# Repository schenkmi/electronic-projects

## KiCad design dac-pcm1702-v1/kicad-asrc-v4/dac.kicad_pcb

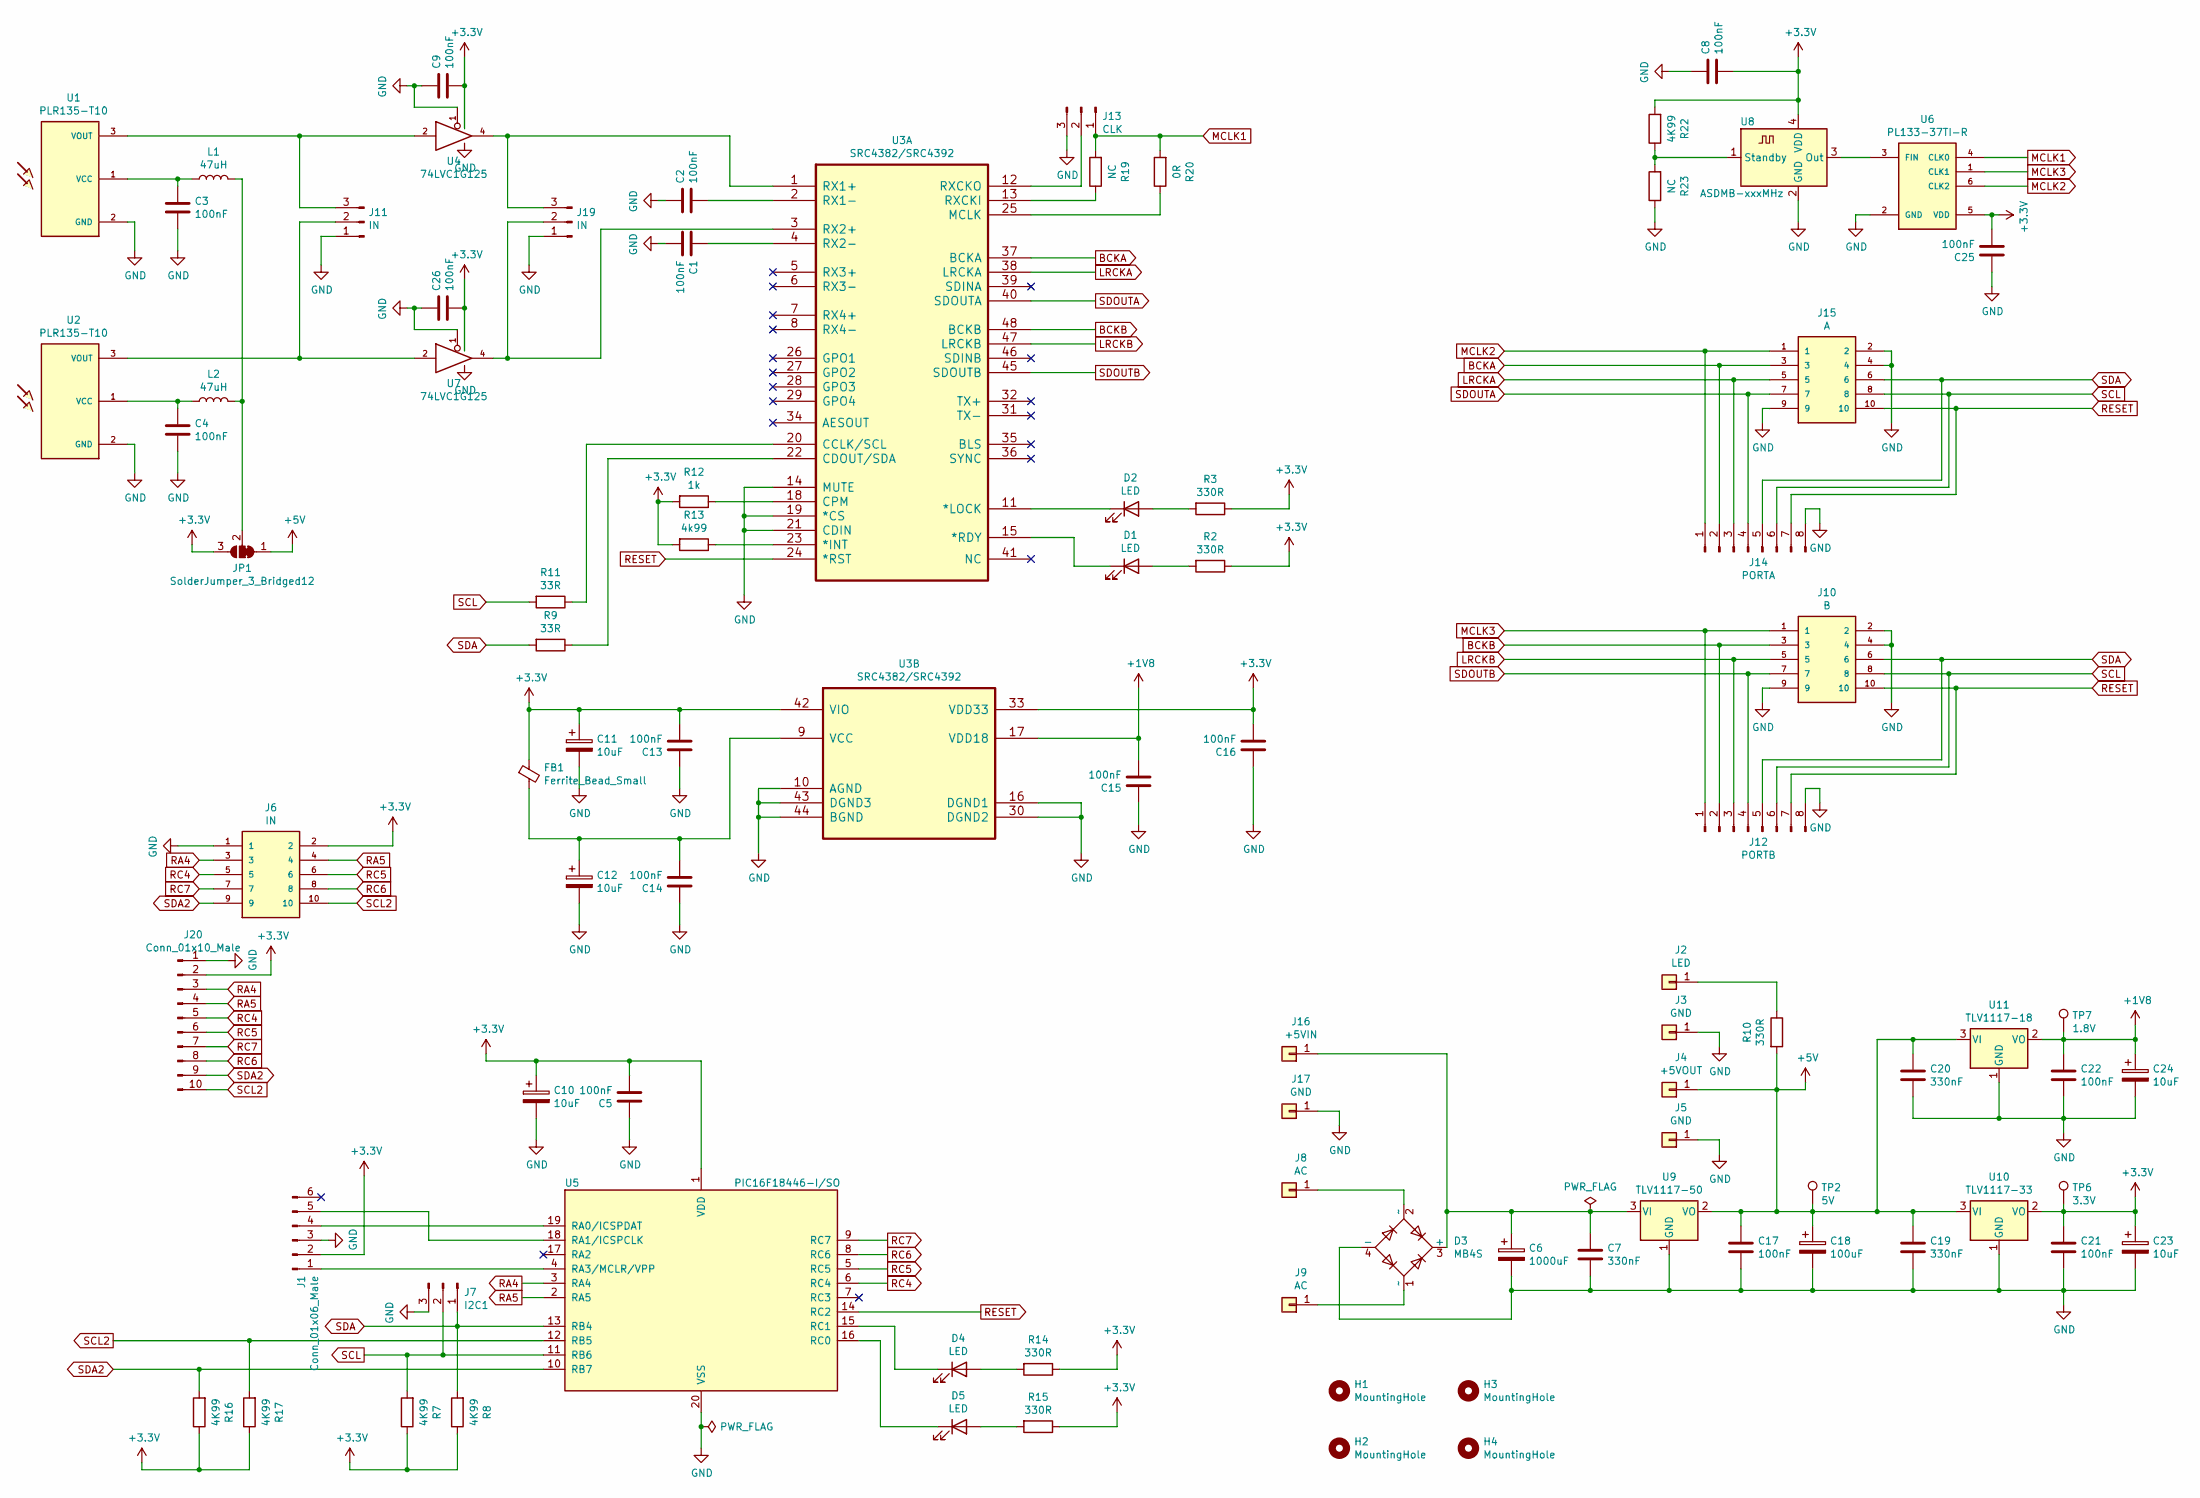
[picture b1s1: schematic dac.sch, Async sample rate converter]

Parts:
C1, C2, C3, C4, C5, C8, C9, C13, C14, C15, C16, C25, C26: 100nF; C_0603_1608Metric_Pad1.08x0.95mm_HandSolder
C6: 1000uF; CP_Radial_D12.5mm_P5.00mm
C7, C19, C20: 330nF; C_0805_2012Metric_Pad1.18x1.45mm_HandSolder
C10, C11, C12, C23, C24: 10uF; CP_EIA-3528-21_Kemet-B_Pad1.50x2.35mm_HandSolder
C17, C21, C22: 100nF; C_0805_2012Metric_Pad1.18x1.45mm_HandSolder
C18: 100uF; CP_Radial_D8.0mm_P3.50mm
D1, D2, D4, D5: LED; LED_0805_2012Metric_Pad1.15x1.40mm_HandSolder
D3: MB4S; TO-269AA
FB1: Ferrite_Bead_Small; C_0603_1608Metric_Pad1.08x0.95mm_HandSolder
H1, H2, H3, H4: MountingHole; MountingHole_3.2mm_M3
J1: Conn_01x06_Male; PinHeader_1x06_P2.54mm_Vertical
J2: LED; Pin_D1.0mm_L10.0mm
J3, J5, J17: GND; Pin_D1.0mm_L10.0mm
J4: +5VOUT; Pin_D1.0mm_L10.0mm
J6: IN; TE_CONN_RCPT_10POS_0.1_TIN_PCB
J7: I2C1; PinHeader_1x03_P2.54mm_Vertical
J8, J9: AC; Pin_D1.0mm_L10.0mm
J10: B; TE_CONN_RCPT_10POS_0.1_TIN_PCB
J11, J19: IN; PinHeader_1x03_P2.54mm_Vertical
J12: PORTB; PinHeader_1x08_P2.54mm_Vertical
J13: CLK; PinHeader_1x03_P2.54mm_Vertical
J14: PORTA; PinHeader_1x08_P2.54mm_Vertical
J15: A; TE_CONN_RCPT_10POS_0.1_TIN_PCB
J16: +5VIN; Pin_D1.0mm_L10.0mm
J20: Conn_01x10_Male; PinHeader_2x05_P2.54mm_Vertical
JP1: SolderJumper_3_Bridged12; SolderJumper-3_P1.3mm_Bridged12_RoundedPad1.0x1.5mm_NumberL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
L1, L2: 47uH; L_0805_2012Metric_Pad1.05x1.20mm_HandSolder
R2, R3, R14, R15: 330R; R_0603_1608Metric_Pad0.98x0.95mm_HandSolder
R7, R8, R16, R17, R22: 4K99; R_0603_1608Metric_Pad0.98x0.95mm_HandSolder
R9, R11: 33R; R_0603_1608Metric_Pad0.98x0.95mm_HandSolder
R10: 330R; R_0805_2012Metric_Pad1.20x1.40mm_HandSolder
R12: 1k; R_0603_1608Metric_Pad0.98x0.95mm_HandSolder
R13: 4k99; R_0603_1608Metric_Pad0.98x0.95mm_HandSolder
R19, R23: NC; R_0603_1608Metric_Pad0.98x0.95mm_HandSolder
R20: 0R; R_0603_1608Metric_Pad0.98x0.95mm_HandSolder
TP2: 5V; TestPoint_Pad_D1.0mm
TP6: 3.3V; TestPoint_Pad_D1.0mm
TP7: 1.8V; TestPoint_Pad_D1.0mm
U1, U2: PLR135-T10; PLR135-T10_PLT133-T10W
U3: SRC4382/SRC4392; TQFP-48_7x7mm_P0.5mm
U4, U7: 74LVC1G125; SOT-353_SC-70-5_Handsoldering
U5: PIC16F18446-I/SO; SOIC-20W_7.5x12.8mm_P1.27mm
U6: PL133-37TI-R; SOT-23-6
U8: ASDMB-xxxMHz; Oscillator_SMD_EuroQuartz_XO91-4Pin_7.0x5.0mm_HandSoldering
U9: TLV1117-50; SOT-223-3_TabPin2
U10: TLV1117-33; SOT-223-3_TabPin2
U11: TLV1117-18; SOT-223-3_TabPin2

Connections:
+1V8: C15.2, C22.1, C24.1, TP7.1, U3.17 (VDD18), U11.2 (VO)
+3V3: C5.2, C8.1, C9.1, C10.1, C11.1, C13.2, C16.2, C21.1, C23.1, C25.2, C26.1, FB1.1, J1.2, J6.2, J20.2, JP1.3 (B), R2.1, R3.1, R7.1, R8.1, R12.2, R13.2, R14.1, R15.1, R16.1, R17.1, R22.2, TP6.1, U3.33 (VDD33), U3.42 (VIO), U4.5 (VCC), U5.1 (VDD), U6.5 (VDD), U7.5 (VCC), U8.4 (VDD), U10.2 (VO)
+5V: C17.1, C18.1, C19.1, C20.1, J4.1, JP1.1 (A), R10.2, TP2.1, U9.2 (VO), U10.3 (VI), U11.3 (VI)
BCKA: J14.2, J15.3, U3.37 (BCKA)
BCKB: J10.3, J12.2, U3.48 (BCKB)
GND: C1.1, C2.2, C3.1, C4.1, C5.1, C6.2, C7.2, C8.2, C9.2, C10.2, C11.2, C12.2, C13.1, C14.1, C15.1, C16.1, C17.2, C18.2, C19.2, C20.2, C21.2, C22.2, C23.2, C24.2, C25.1, C26.2, D3.4 (-), J1.3, J3.1, J5.1, J6.1, J7.3, J10.2, J10.4, J10.9, J11.1, J12.8, J13.3, J14.8, J15.2, J15.4, J15.9, J17.1, J19.1, J20.1, R23.1, U1.2 (GND), U2.2 (GND), U3.10 (AGND), U3.14 (MUTE), U3.16 (DGND1), U3.19 (*CS), U3.21 (CDIN), U3.30 (DGND2), U3.43 (DGND3), U3.44 (BGND), U4.1, U4.3 (GND), U5.20 (VSS), U6.2 (GND), U7.1, U7.3 (GND), U8.2 (GND), U9.1 (GND), U10.1 (GND), U11.1 (GND)
LRCKA: J14.3, J15.5, U3.38 (LRCKA)
LRCKB: J10.5, J12.3, U3.47 (LRCKB)
MCLK1: J13.1, R19.2, R20.2, U6.4 (CLK0)
MCLK2: J14.1, J15.1, U6.6 (CLK2)
MCLK3: J10.1, J12.1, U6.1 (CLK1)
unnamed: C1.2, U3.4 (RX2-)
unnamed: C2.1, U3.2 (RX1-)
unnamed: C3.2, L1.1, U1.1 (VCC)
unnamed: C4.2, L2.1, U2.1 (VCC)
unnamed: C6.1, C7.1, D3.3 (+), J16.1, U9.3 (VI)
unnamed: C12.1, C14.2, FB1.2, U3.9 (VCC)
unnamed: D1.1 (K), U3.15 (*RDY)
unnamed: D1.2 (A), R2.2
unnamed: D2.1 (K), U3.11 (*LOCK)
unnamed: D2.2 (A), R3.2
unnamed: D3.1 (~~), J9.1
unnamed: D3.2 (~~), J8.1
unnamed: D4.1 (K), U5.15 (RC1)
unnamed: D4.2 (A), R14.2
unnamed: D5.1 (K), U5.16 (RC0)
unnamed: D5.2 (A), R15.2
unnamed: J1.1, U5.4 (RA3/MCLR/VPP)
unnamed: J1.4, U5.19 (RA0/ICSPDAT)
unnamed: J1.5, U5.18 (RA1/ICSPCLK)
unnamed: J2.1, R10.1
unnamed: J11.2, U2.3 (VOUT), U7.2
unnamed: J11.3, U1.3 (VOUT), U4.2
unnamed: J13.2, U3.12 (RXCKO)
unnamed: J19.2, U3.3 (RX2+), U7.4
unnamed: J19.3, U3.1 (RX1+), U4.4
unnamed: JP1.2 (C), L1.2, L2.2
unnamed: R9.1, U3.22 (CDOUT/SDA)
unnamed: R11.1, U3.20 (CCLK/SCL)
unnamed: R12.1, U3.18 (CPM)
unnamed: R13.1, U3.23 (*INT)
unnamed: R19.1, U3.13 (RXCKI)
unnamed: R20.1, U3.25 (MCLK)
unnamed: R22.1, R23.2, U8.1 (Standby)
unnamed: U6.3 (FIN), U8.3 (Out)
RA4: J6.3, J20.3, U5.3 (RA4)
RA5: J6.4, J20.4, U5.2 (RA5)
RC4: J6.5, J20.5, U5.6 (RC4)
RC5: J6.6, J20.6, U5.5 (RC5)
RC6: J6.8, J20.8, U5.8 (RC6)
RC7: J6.7, J20.7, U5.9 (RC7)
RESET: J10.10, J12.7, J14.7, J15.10, U3.24 (*RST), U5.14 (RC2)
SCL: J7.2, J10.8, J12.6, J14.6, J15.8, R7.2, R11.2, U5.11 (RB6)
SCL2: J6.10, J20.10, R17.2, U5.12 (RB5)
SDA: J7.1, J10.6, J12.5, J14.5, J15.6, R8.2, R9.2, U5.13 (RB4)
SDA2: J6.9, J20.9, R16.2, U5.10 (RB7)
SDOUTA: J14.4, J15.7, U3.40 (SDOUTA)
SDOUTB: J10.7, J12.4, U3.45 (SDOUTB)

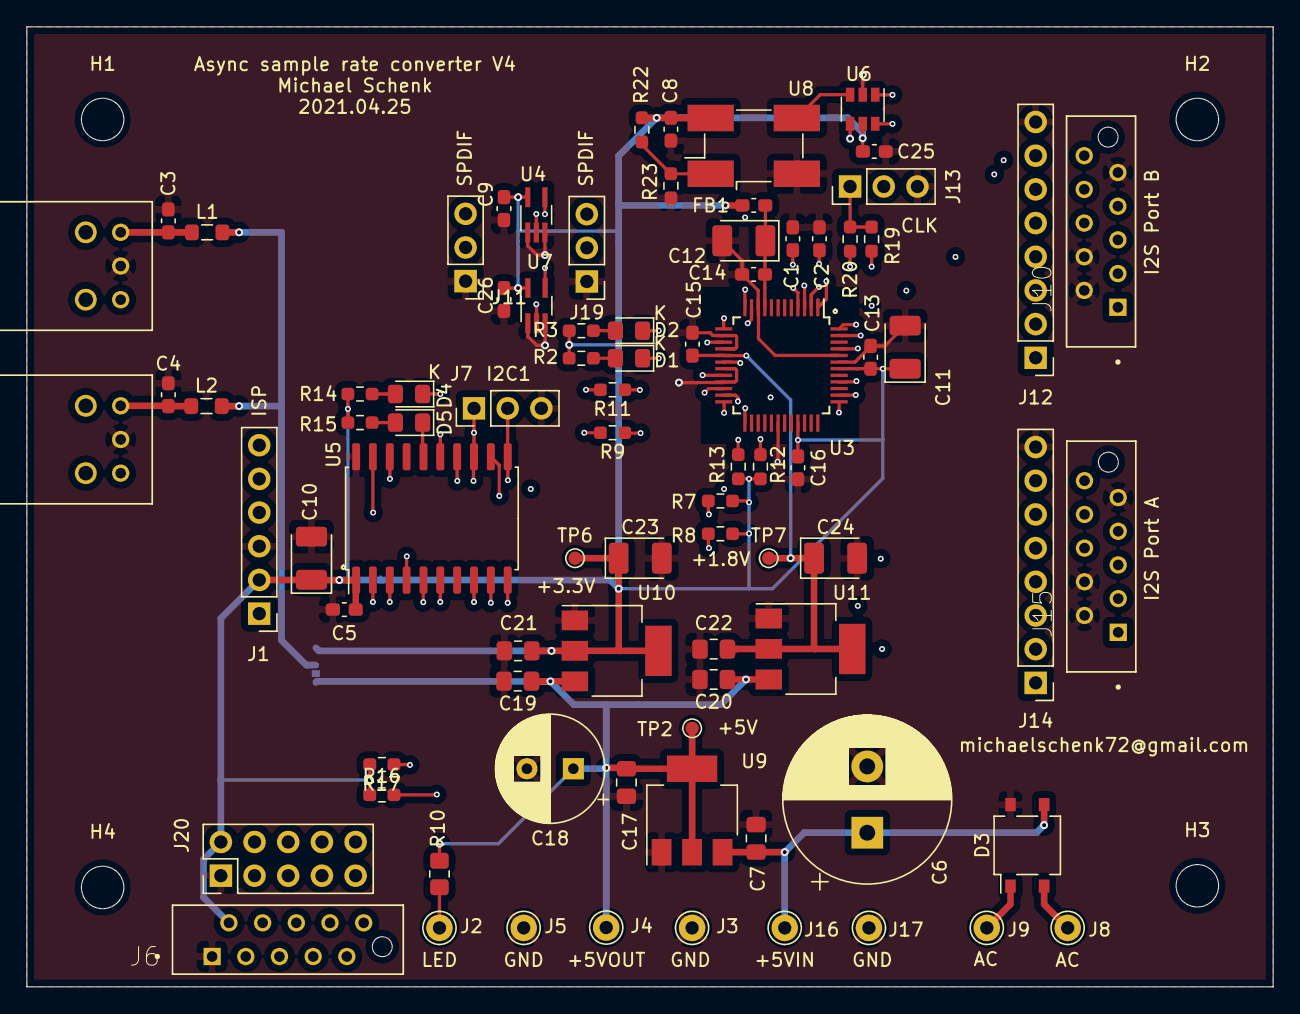
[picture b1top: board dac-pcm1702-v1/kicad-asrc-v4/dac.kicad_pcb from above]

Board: 4 copper layers, 94.0 x 72.4 mm, 89 parts (1 on the bottom side), 58 nets.

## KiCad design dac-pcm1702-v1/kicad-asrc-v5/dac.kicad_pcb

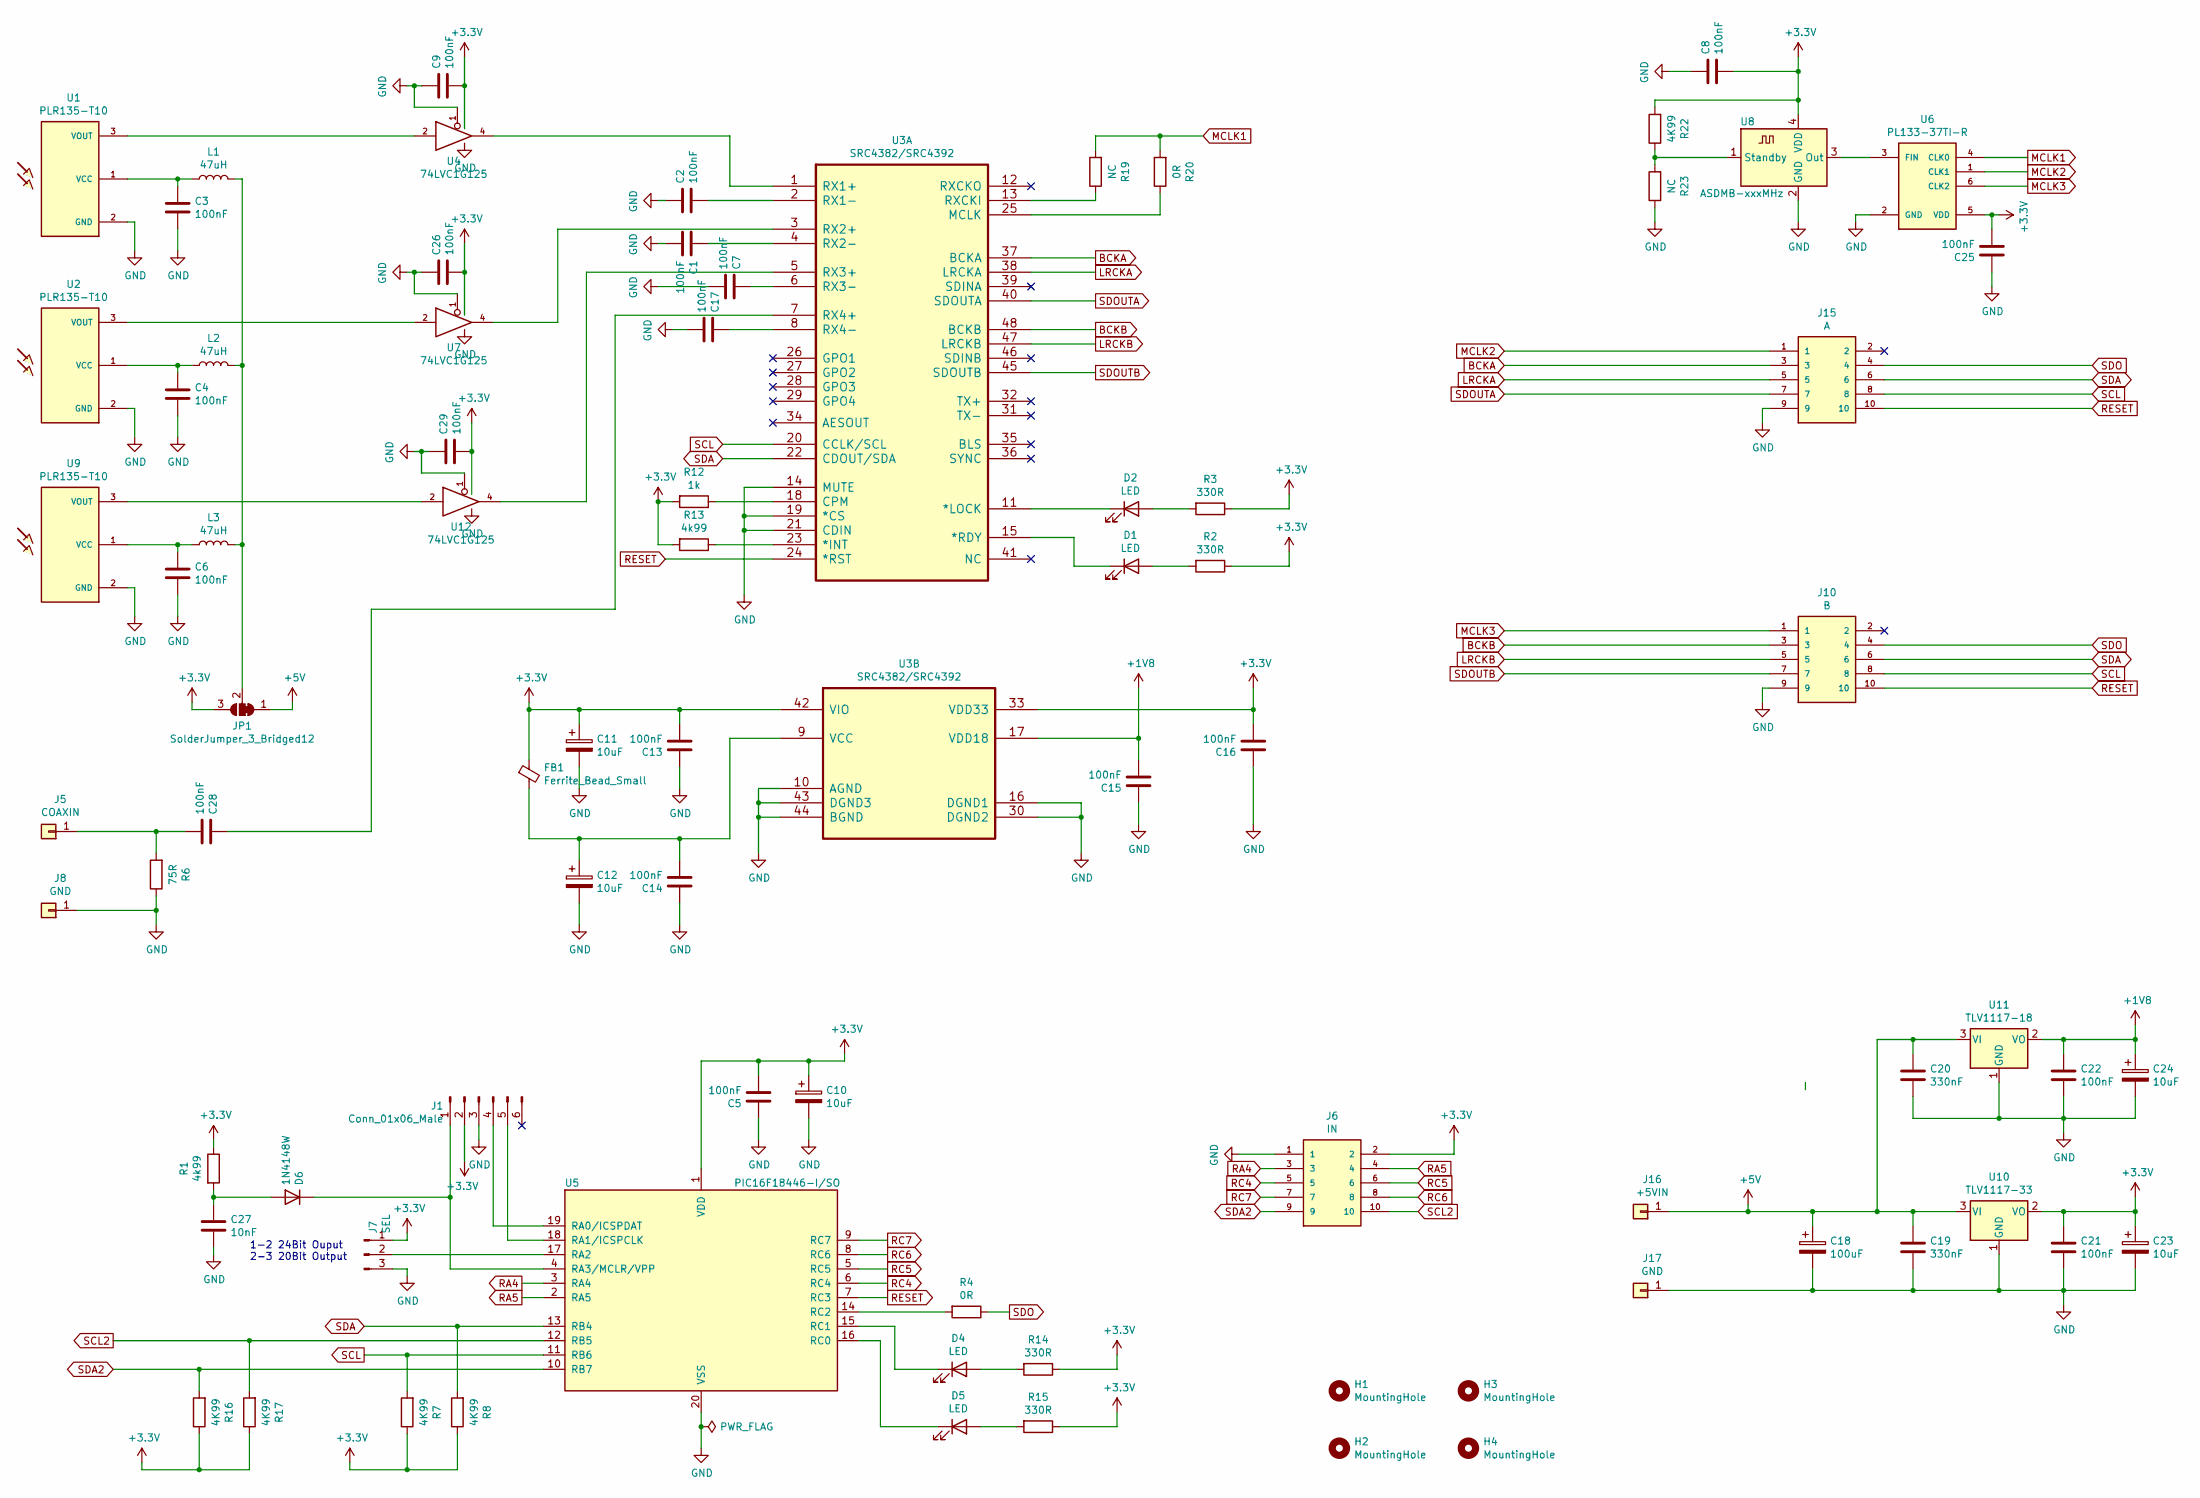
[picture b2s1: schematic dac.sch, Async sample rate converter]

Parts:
C1, C2, C3, C4, C5, C6, C7, C8, C9, C13, C14, C15, C16, C17, C25, C26, C28, C29: 100nF; C_0603_1608Metric_Pad1.08x0.95mm_HandSolder
C10, C11, C12, C23, C24: 10uF; CP_EIA-3528-21_Kemet-B_Pad1.50x2.35mm_HandSolder
C18: 100uF; CP_Radial_D8.0mm_P3.50mm
C19, C20: 330nF; C_0805_2012Metric_Pad1.18x1.45mm_HandSolder
C21, C22: 100nF; C_0805_2012Metric_Pad1.18x1.45mm_HandSolder
C27: 10nF; C_0603_1608Metric_Pad1.08x0.95mm_HandSolder
D1, D2, D4, D5: LED; LED_0805_2012Metric_Pad1.15x1.40mm_HandSolder
D6: 1N4148W; D_SOD-123
FB1: Ferrite_Bead_Small; C_0603_1608Metric_Pad1.08x0.95mm_HandSolder
H1, H2, H3, H4: MountingHole; MountingHole_3.2mm_M3
J1: Conn_01x06_Male; PinHeader_1x06_P2.54mm_Vertical
J5: COAXIN; Pin_D1.0mm_L10.0mm
J6: IN; TE_CONN_RCPT_10POS_0.1_TIN_PCB
J7: SEL; PinHeader_1x03_P2.54mm_Vertical
J8, J17: GND; Pin_D1.0mm_L10.0mm
J10: B; TE_CONN_RCPT_10POS_0.1_TIN_PCB
J15: A; TE_CONN_RCPT_10POS_0.1_TIN_PCB
J16: +5VIN; Pin_D1.0mm_L10.0mm
JP1: SolderJumper_3_Bridged12; SolderJumper-3_P1.3mm_Bridged12_RoundedPad1.0x1.5mm_NumberL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
L1, L2, L3: 47uH; L_0805_2012Metric_Pad1.05x1.20mm_HandSolder
R1, R13: 4k99; R_0603_1608Metric_Pad0.98x0.95mm_HandSolder
R2, R3, R14, R15: 330R; R_0603_1608Metric_Pad0.98x0.95mm_HandSolder
R4, R20: 0R; R_0603_1608Metric_Pad0.98x0.95mm_HandSolder
R6: 75R; R_0603_1608Metric_Pad0.98x0.95mm_HandSolder
R7, R8, R16, R17, R22: 4K99; R_0603_1608Metric_Pad0.98x0.95mm_HandSolder
R12: 1k; R_0603_1608Metric_Pad0.98x0.95mm_HandSolder
R19, R23: NC; R_0603_1608Metric_Pad0.98x0.95mm_HandSolder
U1, U2, U9: PLR135-T10; PLR135-T10_PLT133-T10W
U3: SRC4382/SRC4392; TQFP-48_7x7mm_P0.5mm
U4, U7, U12: 74LVC1G125; SOT-353_SC-70-5_Handsoldering
U5: PIC16F18446-I/SO; SOIC-20W_7.5x12.8mm_P1.27mm
U6: PL133-37TI-R; SOT-23-6
U8: ASDMB-xxxMHz; Oscillator_SMD_EuroQuartz_XO91-4Pin_7.0x5.0mm_HandSoldering
U10: TLV1117-33; SOT-223-3_TabPin2
U11: TLV1117-18; SOT-223-3_TabPin2

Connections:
+1V8: C15.2, C22.1, C24.1, U3.17 (VDD18), U11.2 (VO)
+3V3: C5.2, C8.1, C9.1, C10.1, C11.1, C13.2, C16.2, C21.1, C23.1, C25.2, C26.1, C29.1, FB1.1, J1.2, J6.2, J7.1, JP1.3 (B), R1.1, R2.1, R3.1, R7.1, R8.1, R12.2, R13.2, R14.1, R15.1, R16.1, R17.1, R22.2, U3.33 (VDD33), U3.42 (VIO), U4.5 (VCC), U5.1 (VDD), U6.5 (VDD), U7.5 (VCC), U8.4 (VDD), U10.2 (VO), U12.5 (VCC)
+5V: C18.1, C19.1, C20.1, J16.1, JP1.1 (A), U10.3 (VI), U11.3 (VI)
BCKA: J15.3, U3.37 (BCKA)
BCKB: J10.3, U3.48 (BCKB)
GND: C1.1, C2.2, C3.1, C4.1, C5.1, C6.1, C7.1, C8.2, C9.2, C10.2, C11.2, C12.2, C13.1, C14.1, C15.1, C16.1, C17.1, C18.2, C19.2, C20.2, C21.2, C22.2, C23.2, C24.2, C25.1, C26.2, C27.2, C29.2, J1.3, J6.1, J7.3, J8.1, J10.9, J15.9, J17.1, R6.1, R23.1, U1.2 (GND), U2.2 (GND), U3.10 (AGND), U3.14 (MUTE), U3.16 (DGND1), U3.19 (*CS), U3.21 (CDIN), U3.30 (DGND2), U3.43 (DGND3), U3.44 (BGND), U4.1, U4.3 (GND), U5.20 (VSS), U6.2 (GND), U7.1, U7.3 (GND), U8.2 (GND), U9.2 (GND), U10.1 (GND), U11.1 (GND), U12.1, U12.3 (GND)
LRCKA: J15.5, U3.38 (LRCKA)
LRCKB: J10.5, U3.47 (LRCKB)
MCLK1: R19.2, R20.2, U6.4 (CLK0)
MCLK2: J15.1, U6.1 (CLK1)
MCLK3: J10.1, U6.6 (CLK2)
unnamed: C1.2, U3.4 (RX2-)
unnamed: C2.1, U3.2 (RX1-)
unnamed: C3.2, L1.1, U1.1 (VCC)
unnamed: C4.2, L2.1, U2.1 (VCC)
unnamed: C6.2, L3.1, U9.1 (VCC)
unnamed: C7.2, U3.6 (RX3-)
unnamed: C12.1, C14.2, FB1.2, U3.9 (VCC)
unnamed: C17.2, U3.8 (RX4-)
unnamed: C27.1, D6.2 (A), R1.2
unnamed: C28.1, J5.1, R6.2
unnamed: C28.2, U3.7 (RX4+)
unnamed: D1.1 (K), U3.15 (*RDY)
unnamed: D1.2 (A), R2.2
unnamed: D2.1 (K), U3.11 (*LOCK)
unnamed: D2.2 (A), R3.2
unnamed: D4.1 (K), U5.15 (RC1)
unnamed: D4.2 (A), R14.2
unnamed: D5.1 (K), U5.16 (RC0)
unnamed: D5.2 (A), R15.2
unnamed: D6.1 (K), J1.1, U5.4 (RA3/MCLR/VPP)
unnamed: J1.4, U5.19 (RA0/ICSPDAT)
unnamed: J1.5, U5.18 (RA1/ICSPCLK)
unnamed: J7.2, U5.17 (RA2)
unnamed: JP1.2 (C), L1.2, L2.2, L3.2
unnamed: R4.2, U5.14 (RC2)
unnamed: R12.1, U3.18 (CPM)
unnamed: R13.1, U3.23 (*INT)
unnamed: R19.1, U3.13 (RXCKI)
unnamed: R20.1, U3.25 (MCLK)
unnamed: R22.1, R23.2, U8.1 (Standby)
unnamed: U1.3 (VOUT), U4.2
unnamed: U2.3 (VOUT), U7.2
unnamed: U3.1 (RX1+), U4.4
unnamed: U3.3 (RX2+), U7.4
unnamed: U6.3 (FIN), U8.3 (Out)
unnamed: U9.3 (VOUT), U12.2
unnamed: U3.5 (RX3+), U12.4
RA4: J6.3, U5.3 (RA4)
RA5: J6.4, U5.2 (RA5)
RC4: J6.5, U5.6 (RC4)
RC5: J6.6, U5.5 (RC5)
RC6: J6.8, U5.8 (RC6)
RC7: J6.7, U5.9 (RC7)
RESET: J10.10, J15.10, U3.24 (*RST), U5.7 (RC3)
SCL: J10.8, J15.8, R7.2, U3.20 (CCLK/SCL), U5.11 (RB6)
SCL2: J6.10, R17.2, U5.12 (RB5)
SDA: J10.6, J15.6, R8.2, U3.22 (CDOUT/SDA), U5.13 (RB4)
SDA2: J6.9, R16.2, U5.10 (RB7)
SDO: J10.4, J15.4, R4.1
SDOUTA: J15.7, U3.40 (SDOUTA)
SDOUTB: J10.7, U3.45 (SDOUTB)

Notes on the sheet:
1-2 24Bit Ouput 2-3 20Bit Output

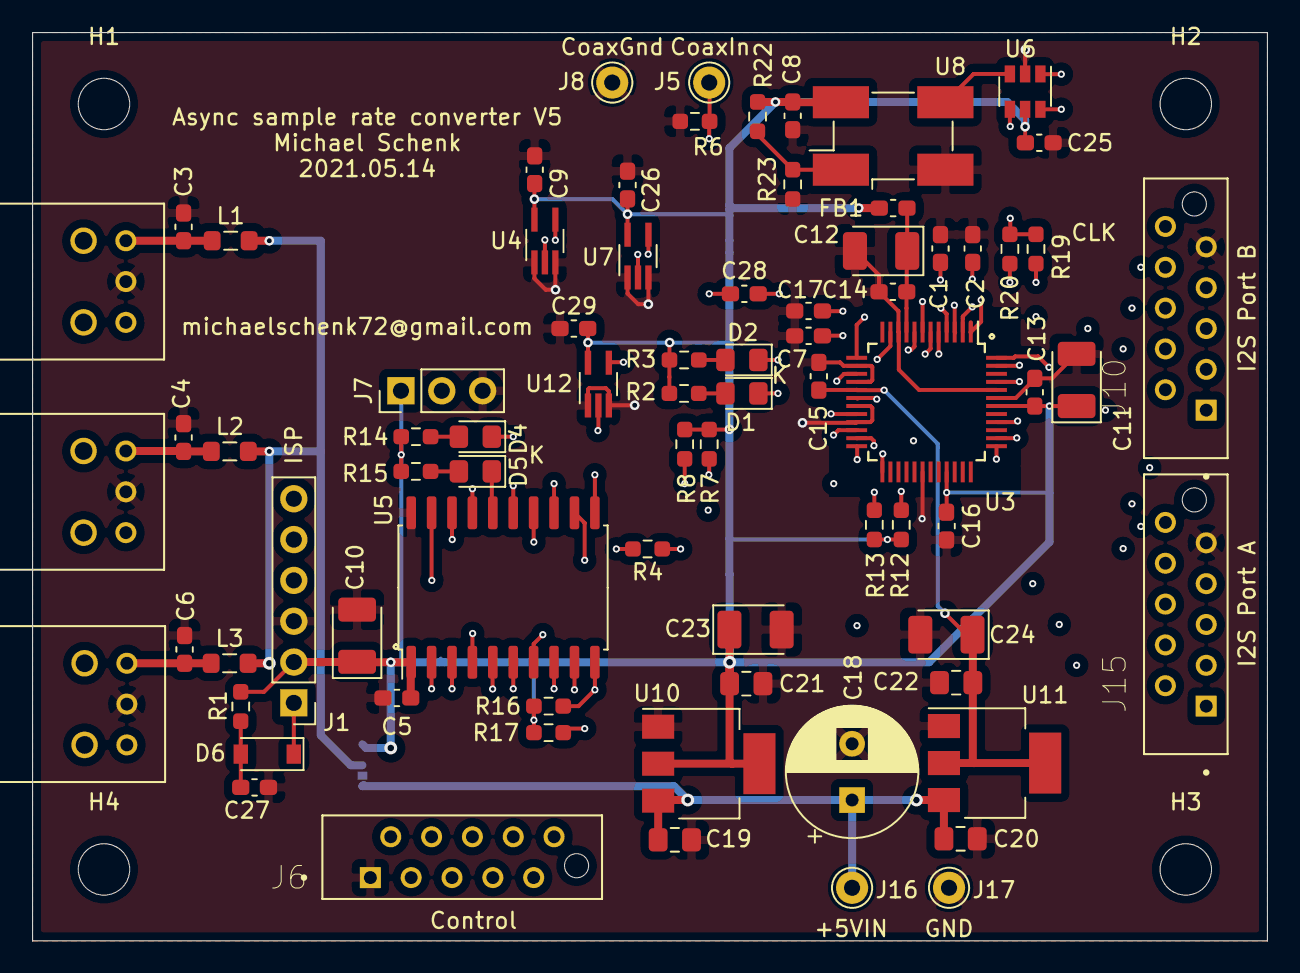
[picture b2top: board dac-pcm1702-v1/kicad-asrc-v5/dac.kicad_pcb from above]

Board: 4 copper layers, 76.8 x 56.5 mm, 81 parts (1 on the bottom side), 62 nets.

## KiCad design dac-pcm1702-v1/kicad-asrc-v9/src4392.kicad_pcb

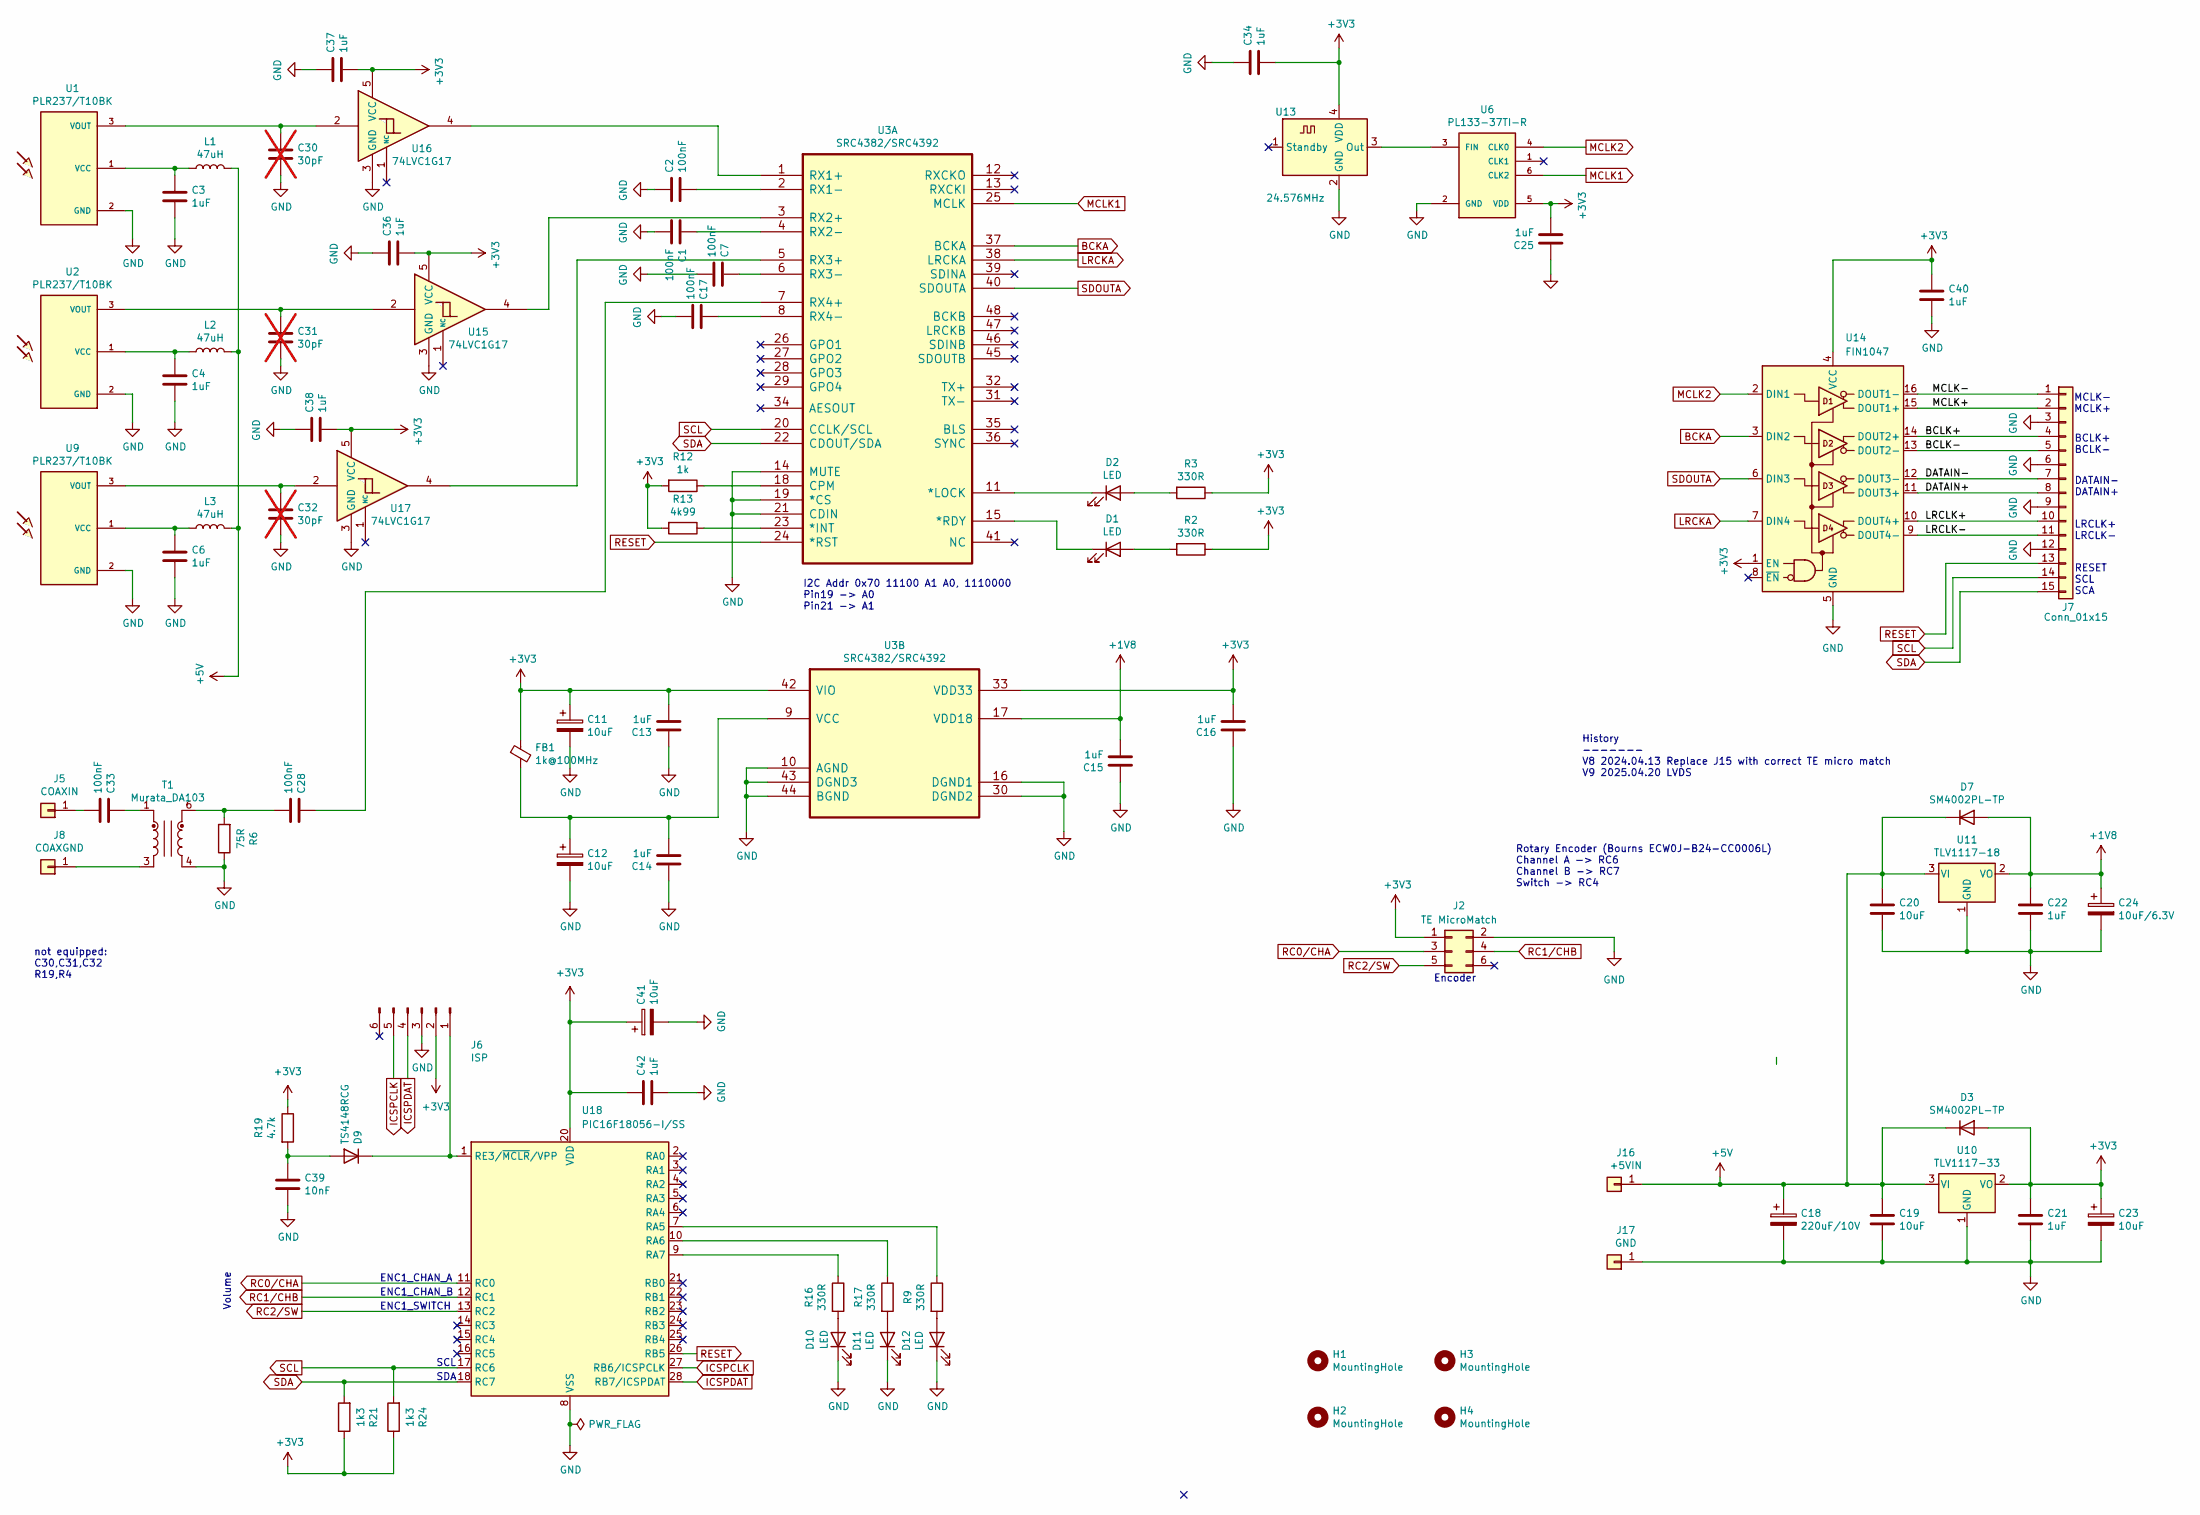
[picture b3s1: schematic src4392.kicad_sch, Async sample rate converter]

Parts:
C1, C2, C7, C17: 100nF; C_0402_1005Metric_Pad0.74x0.62mm_HandSolder
C3, C4, C6, C13, C14, C15, C16, C25, C34, C36, C37, C38, C40, C42: 1uF; C_0603_1608Metric_Pad1.08x0.95mm_HandSolder
C11, C12, C23, C41: 10uF; CP_EIA-2012-12_Kemet-R_HandSolder
C18: 220uF/10V; CP_Radial_D6.3mm_P2.50mm
C19, C20: 10uF; C_1206_3216Metric_Pad1.33x1.80mm_HandSolder
C21, C22: 1uF; C_0805_2012Metric_Pad1.18x1.45mm_HandSolder
C24: 10uF/6.3V; CP_EIA-2012-12_Kemet-R_HandSolder
C28, C33: 100nF; C_0603_1608Metric_Pad1.08x0.95mm_HandSolder
C30, C31, C32: 30pF; C_0603_1608Metric_Pad1.08x0.95mm_HandSolder; not fitted
C39: 10nF; C_0603_1608Metric_Pad1.08x0.95mm_HandSolder
D1, D2, D10, D11, D12: LED; LED_0603_1608Metric_Pad1.05x0.95mm_HandSolder
D3, D7: SM4002PL-TP; D_SOD-123F
D9: TS4148RCG; D_0603_1608Metric_Pad1.05x0.95mm_HandSolder
FB1: 1k@100MHz; C_0603_1608Metric_Pad1.08x0.95mm_HandSolder
H1, H2, H3, H4: MountingHole; MountingHole_3.2mm_M3_Pad_Via
J2: TE MicroMatch; TE_Micro-MaTch_215079-6_2x03_P1.27mm_Vertical
J5: COAXIN; Pin_D1.0mm_L10.0mm
J6: ISP; PinHeader_1x06_P2.54mm_Vertical
J7: Conn_01x15; Molex_502231-1500_1x15-1SH_P0.5mm_Vertical
J8: COAXGND; Pin_D1.0mm_L10.0mm
J16: +5VIN; Pin_D1.0mm_L10.0mm
J17: GND; Pin_D1.0mm_L10.0mm
L1, L2, L3: 47uH; L_0805_2012Metric_Pad1.05x1.20mm_HandSolder
R2, R3, R9, R16, R17: 330R; R_0603_1608Metric_Pad0.98x0.95mm_HandSolder
R6: 75R; R_0603_1608Metric_Pad0.98x0.95mm_HandSolder
R12: 1k; R_0402_1005Metric_Pad0.72x0.64mm_HandSolder
R13: 4k99; R_0402_1005Metric_Pad0.72x0.64mm_HandSolder
R19: 4.7k; R_0603_1608Metric_Pad0.98x0.95mm_HandSolder
R21, R24: 1k3; R_0603_1608Metric_Pad0.98x0.95mm_HandSolder
T1: Murata_DA103; DA100J
U1, U2, U9: PLR237/T10BK; PLR135-T10_PLT133-T10W
U3: SRC4382/SRC4392; TQFP-48_7x7mm_P0.5mm
U6: PL133-37TI-R; SOT-23-6
U10: TLV1117-33; SOT-223-3_TabPin2
U11: TLV1117-18; SOT-223-3_TabPin2
U13: 24.576MHz; Oscillator_SMD_EuroQuartz_XO32-4Pin_3.2x2.5mm_HandSoldering
U14: FIN1047; TSSOP-16_4.4x5mm_P0.65mm; Part Number FIN1047MTCX
U15, U16, U17: 74LVC1G17; SOT-23-5
U18: PIC16F18056-I/SS; SSOP-28_5.3x10.2mm_P0.65mm

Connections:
+1V8: C15.2, C22.1, C24.1, D7.2 (A), U3.17 (VDD18), U11.2 (VO)
+3V3: C11.1, C13.2, C16.2, C21.1, C23.1, C25.2, C34.1, C36.1, C37.1, C38.1, C40.1, C41.1, C42.1, D3.2 (A), FB1.1, J2.1, J6.2, R2.1, R3.1, R12.2, R13.2, R19.1, R21.1, R24.1, U3.33 (VDD33), U3.42 (VIO), U6.5 (VDD), U10.2 (VO), U13.4 (VDD), U14.1 (EN), U14.4 (VCC), U15.5 (VCC), U16.5 (VCC), U17.5 (VCC), U18.20 (VDD)
+5V: C18.1, C19.1, C20.1, D3.1 (K), D7.1 (K), J16.1, L1.2, L2.2, L3.2, U10.3 (VI), U11.3 (VI)
/BCLK+: J7.4, U14.14 (DOUT2+)
/BCLK-: J7.5, U14.13 (DOUT2-)
/DATAIN+: J7.8, U14.11 (DOUT3+)
/DATAIN-: J7.7, U14.12 (DOUT3-)
/LRCLK+: J7.10, U14.10 (DOUT4+)
/LRCLK-: J7.11, U14.9 (DOUT4-)
/MCLK+: J7.2, U14.15 (DOUT1+)
/MCLK-: J7.1, U14.16 (DOUT1-)
BCKA: U3.37 (BCKA), U14.3 (DIN2)
GND: C1.1, C2.2, C3.1, C4.1, C6.1, C7.1, C11.2, C12.2, C13.1, C14.1, C15.1, C16.1, C17.1, C18.2, C19.2, C20.2, C21.2, C22.2, C23.2, C24.2, C25.1, C30.1, C31.1, C32.1, C34.2, C36.2, C37.2, C38.2, C39.2, C40.2, C41.2, C42.2, D10.1 (K), D11.1 (K), D12.1 (K), J2.2, J6.3, J7.3, J7.6, J7.9, J7.12, J17.1, R6.1, T1.4, U1.2 (GND), U2.2 (GND), U3.10 (AGND), U3.14 (MUTE), U3.16 (DGND1), U3.19 (*CS), U3.21 (CDIN), U3.30 (DGND2), U3.43 (DGND3), U3.44 (BGND), U6.2 (GND), U9.2 (GND), U10.1 (GND), U11.1 (GND), U13.2 (GND), U14.5 (GND), U15.3 (GND), U16.3 (GND), U17.3 (GND), U18.8 (VSS), U18.19 (VSS)
ICSPCLK: J6.5, U18.27 (RB6/ICSPCLK)
ICSPDAT: J6.4, U18.28 (RB7/ICSPDAT)
LRCKA: U3.38 (LRCKA), U14.7 (DIN4)
MCLK1: U3.25 (MCLK), U6.6 (CLK2)
MCLK2: U6.4 (CLK0), U14.2 (DIN1)
unnamed: C28.1, R6.2, T1.6
unnamed: C33.2, T1.1
unnamed: D1.2 (A), R2.2
unnamed: D1.1 (K), U3.15 (*RDY)
unnamed: D2.2 (A), R3.2
unnamed: D2.1 (K), U3.11 (*LOCK)
unnamed: C39.1, D9.2 (A), R19.2
unnamed: D9.1 (K), J6.1, U18.1 (RE3/~MCLR/VPP)
unnamed: D10.2 (A), R16.2
unnamed: D11.2 (A), R17.2
unnamed: D12.2 (A), R9.2
unnamed: C33.1, J5.1
unnamed: J8.1, T1.3
unnamed: C3.2, L1.1, U1.1 (VCC)
unnamed: C30.2, U1.3 (VOUT), U16.2
unnamed: C4.2, L2.1, U2.1 (VCC)
unnamed: C31.2, U2.3 (VOUT), U15.2
unnamed: R13.1, U3.23 (*INT)
unnamed: R12.1, U3.18 (CPM)
unnamed: U3.1 (RX1+), U16.4
unnamed: C2.1, U3.2 (RX1-)
unnamed: U3.3 (RX2+), U15.4
unnamed: C1.2, U3.4 (RX2-)
unnamed: U3.5 (RX3+), U17.4
unnamed: C7.2, U3.6 (RX3-)
unnamed: C28.2, U3.7 (RX4+)
unnamed: C17.2, U3.8 (RX4-)
unnamed: C12.1, C14.2, FB1.2, U3.9 (VCC)
unnamed: C6.2, L3.1, U9.1 (VCC)
unnamed: C32.2, U9.3 (VOUT), U17.2
unnamed: U6.3 (FIN), U13.3 (Out)
unnamed: R9.1, U18.7 (RA5)
unnamed: R17.1, U18.10 (RA6)
unnamed: R16.1, U18.9 (RA7)
RC0/CHA: J2.3, U18.11 (RC0)
RC1/CHB: J2.4, U18.12 (RC1)
RC2/SW: J2.5, U18.13 (RC2)
RESET: J7.13, U3.24 (*RST), U18.26 (RB5)
SCL: J7.14, R24.2, U3.20 (CCLK/SCL), U18.17 (RC6)
SDA: J7.15, R21.2, U3.22 (CDOUT/SDA), U18.18 (RC7)
SDOUTA: U3.40 (SDOUTA), U14.6 (DIN3)

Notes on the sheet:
ENC1_CHAN_B
I2C Addr 0x70 11100 A1 A0, 1110000 Pin19 -> A0 Pin21 -> A1
History ------- V8 2024.04.13 Replace J15 with correct TE micro match V9 2025.04.20 LVDS
ENC1_CHAN_A
SDA
DATAIN- DATAIN+
LRCLK+ LRCLK-
MCLK- MCLK+
ENC1_SWITCH
Rotary Encoder (Bourns ECW0J-B24-CC0006L) Channel A -> RC6 Channel B -> RC7 Switch -> RC4
Volume
BCLK+ BCLK-
Encoder
not equipped: C30,C31,C32 R19,R4
SCL
RESET SCL SCA
